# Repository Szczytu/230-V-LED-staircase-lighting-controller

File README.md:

# 230-V-LED-staircase-lighting-controller
Controller for a large staircase consisting of 3 parts, total 26 stairs on 230 V LED strips. The controller has a built-in twilight sensor, the sensitivity of which can be adjusted using a potentiometer.
The construction of the controller was due to an unusual staircase and the desire not to use a separate power supply for 12-24V LEDs 
# Schematic and project controller of 230V LED
The project schematic, sample 3D model and gerber file is in the folder "PCB_162x104mm_LED_STAIRS"
The project was made in KiCad 8.0.
## Schematic

## Simplified schematic

> [!IMPORTANT]
> 1 leg of the BT136 triac is connected to the PHASE of the LED strip. The 2nd leg of the BT136 triac is connected to the PHASE of the AC mains. The 3rd leg of the BT136 triac is connected to the gate of the power3061 controller.

> [!CAUTION]
> DO NOT SWAP THE CONNECTION FROM THE 1ST LEG WITH THE 2ND LEG OF THE BT-136 TRIAC BECAUSE IT WILL NOT WORK!

## 3D model

## Final efect of the controller
A universal Kradex Z112A plastic housing with dimensions of 186x136x40mm was used to enclose the PCB

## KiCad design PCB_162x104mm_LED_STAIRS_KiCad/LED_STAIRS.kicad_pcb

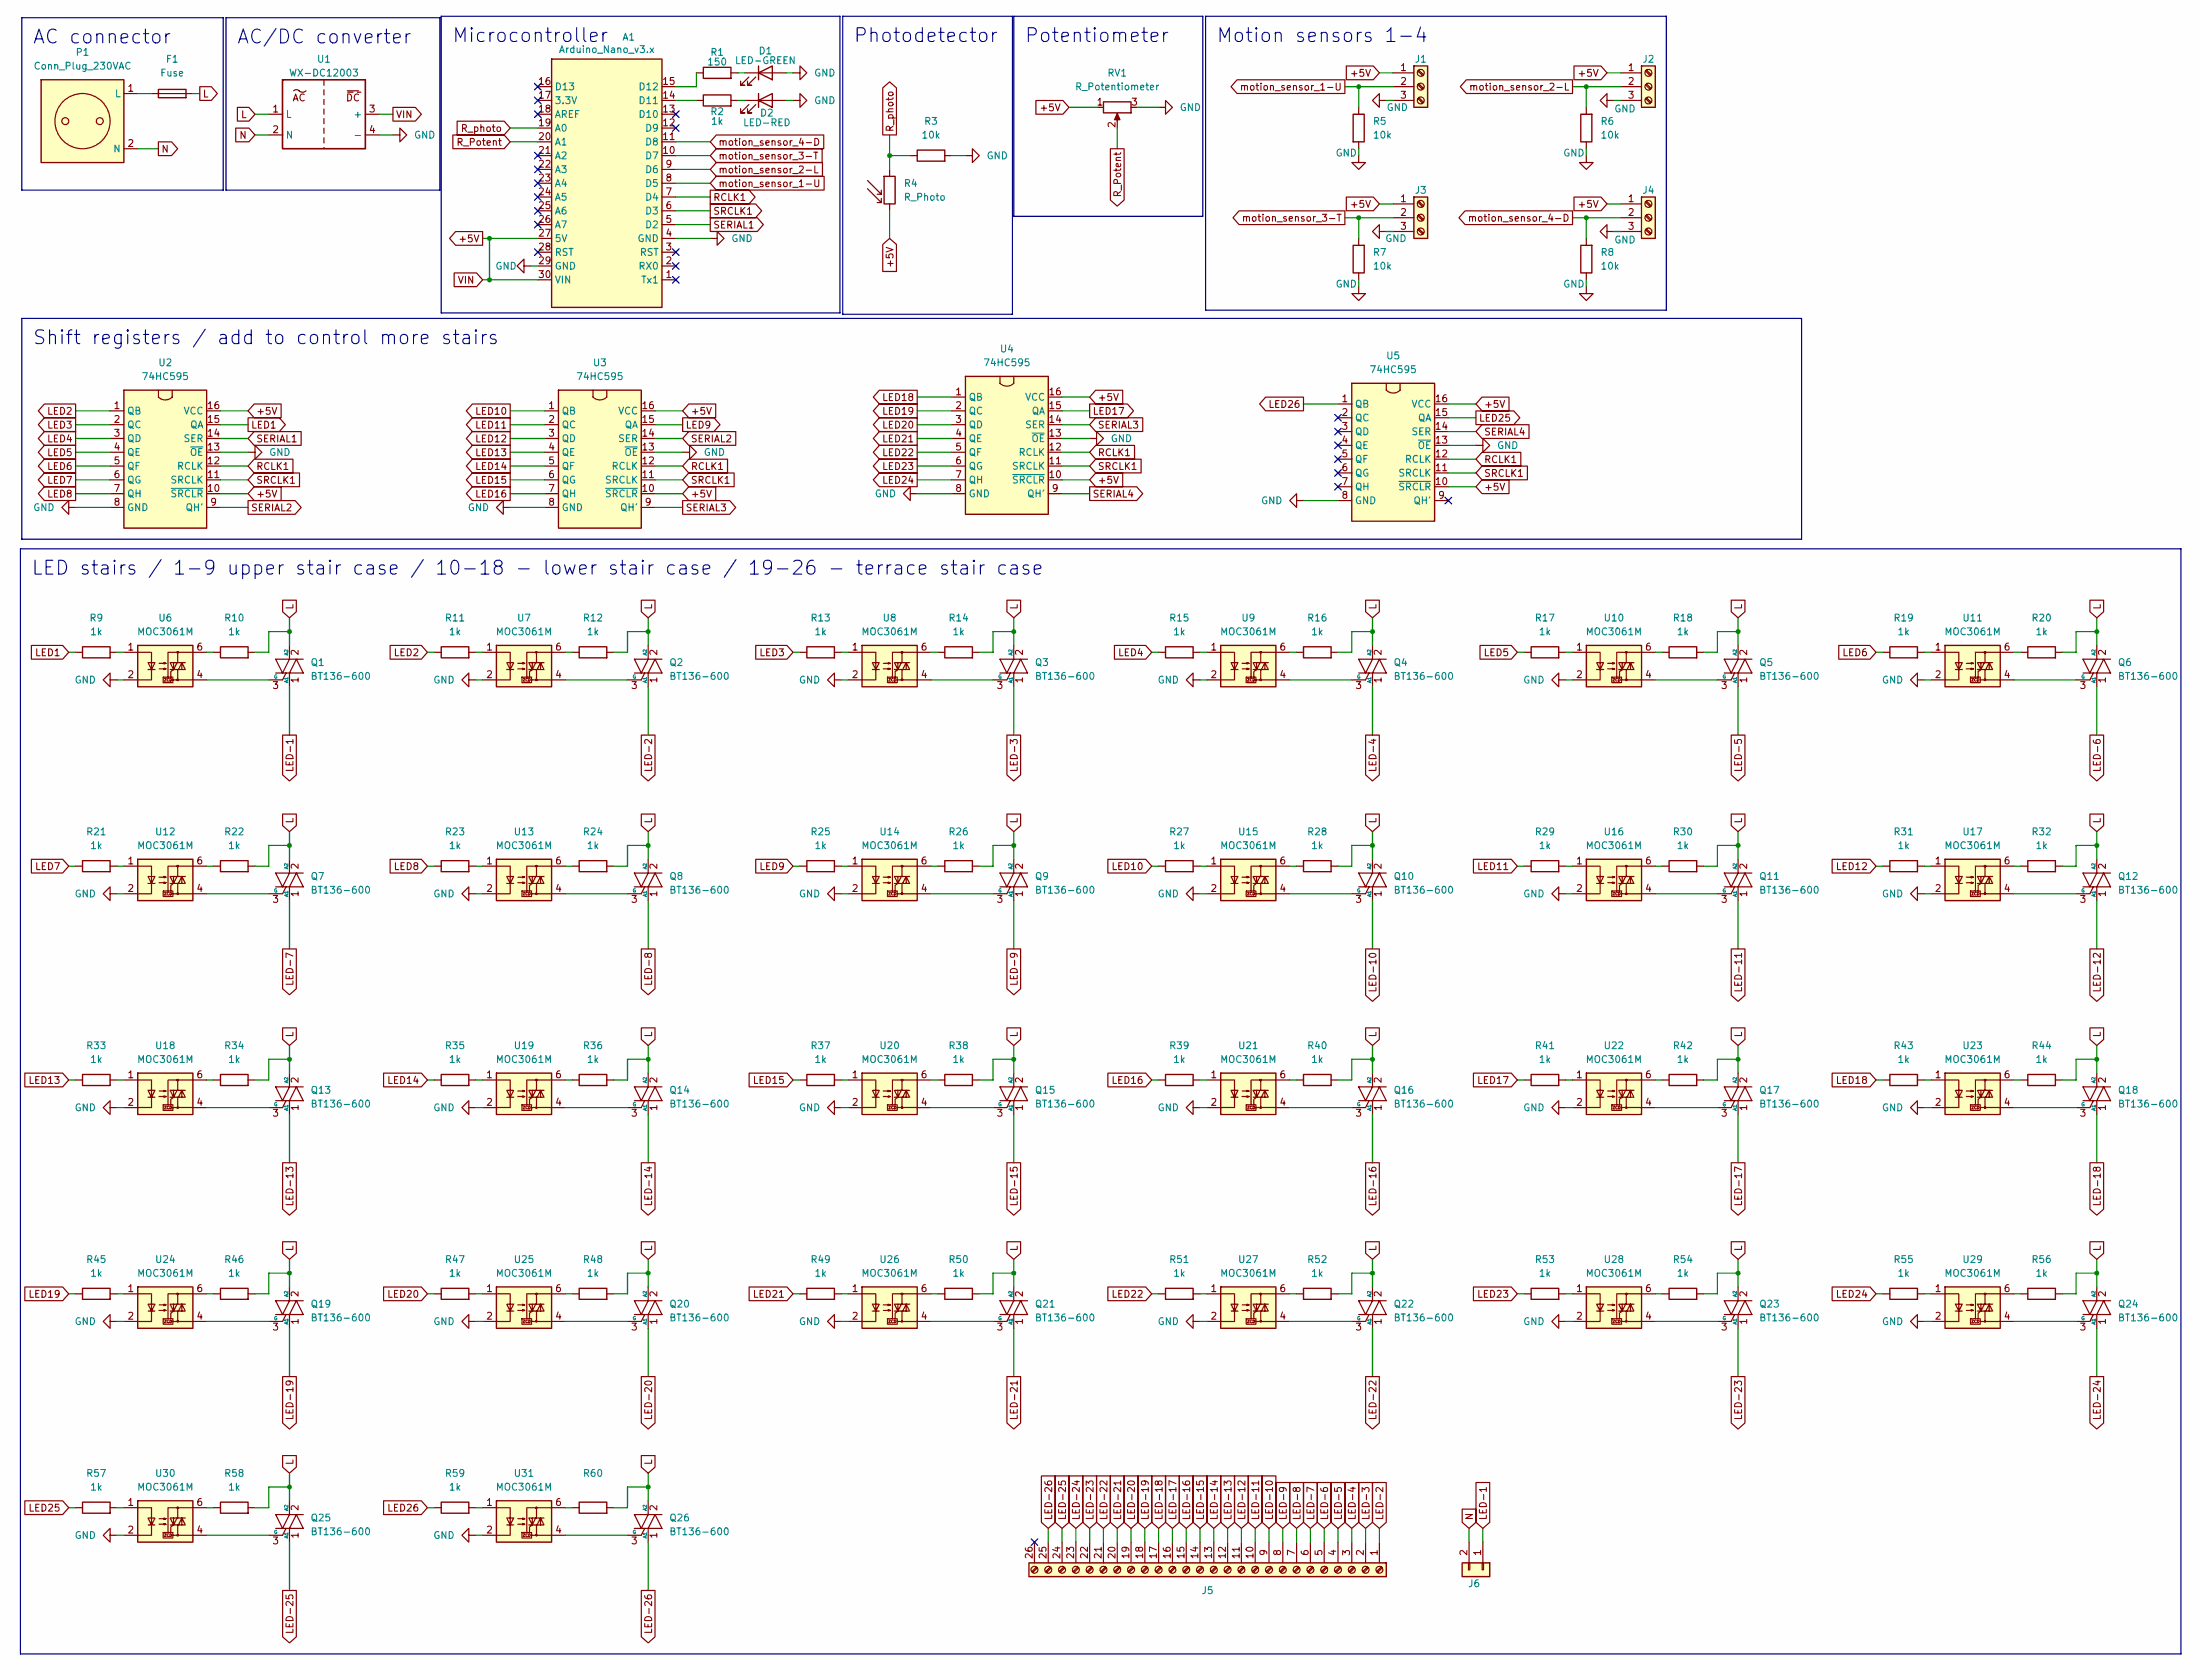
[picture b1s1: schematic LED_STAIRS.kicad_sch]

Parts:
A1: Arduino_Nano_v3.x; Arduino_Nano
D1: LED-GREEN; R_Axial_DIN0204_L3.6mm_D1.6mm_P2.54mm_Vertical
D2: LED-RED; R_Axial_DIN0204_L3.6mm_D1.6mm_P2.54mm_Vertical
F1: Fuse; Fuseholder_Cylinder-5x20mm_Stelvio-Kontek_PTF78_Horizontal_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
J1, J2, J3, J4: Screw_Terminal_01x03; terminalx03x2.5mmPitch
J5: Screw_Terminal_01x26; terminalx26x2.5mmPitch
J6: Conn_01x02; terminalx02x2.5mmPitch
P1: Conn_Plug_230VAC; terminalx02x2.5mmPitch
Q1, Q2, Q3, Q4, Q5, Q6, Q7, Q8, Q9, Q10, Q11, Q12, Q13, Q14, Q15, Q16, Q17, Q18, Q19, Q20, Q21, Q22, Q23, Q24, Q25, Q26: BT136-600; TO-220-3_Vertical
R1: 150; R_Axial_DIN0207_L6.3mm_D2.5mm_P10.16mm_Horizontal
R2, R9, R10, R11, R12, R13, R14, R15, R16, R17, R18, R19, R20, R21, R22, R23, R24, R25, R26, R27, R28, R29, R30, R31, R32, R33, R34, R35, R36, R37, R38, R39, R40, R41, R42, R43, R44, R45, R46, R47, R48, R49, R50, R51, R52, R53, R54, R55, R56, R57, R58, R59, R60: 1k; R_Axial_DIN0207_L6.3mm_D2.5mm_P10.16mm_Horizontal
R3, R5, R6, R7, R8: 10k; R_Axial_DIN0207_L6.3mm_D2.5mm_P10.16mm_Horizontal
R4: R_Photo; R_Axial_DIN0204_L3.6mm_D1.6mm_P2.54mm_Vertical
RV1: R_Potentiometer; Potentiometer_5k
U1: WX-DC12003
U2, U3, U4, U5: 74HC595; 74HC595N
U6, U7, U8, U9, U10, U11, U12, U13, U14, U15, U16, U17, U18, U19, U20, U21, U22, U23, U24, U25, U26, U27, U28, U29, U30, U31: MOC3061M; moc3021

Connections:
+5V: A1.27 (5V), A1.30 (VIN), J1.1, J2.1, J3.1, J4.1, R4.2, RV1.1, U1.3 (+), U2.10 (~SRCLR), U2.16 (VCC), U3.10 (~SRCLR), U3.16 (VCC), U4.10 (~SRCLR), U4.16 (VCC), U5.10 (~SRCLR), U5.16 (VCC); also elsewhere on the board
GND: A1.4 (GND), A1.29 (GND), D1.2 (A), D2.2 (A), J1.3, J2.3, J3.3, J4.3, R3.2, R5.2, R6.1, R7.1, R8.1, RV1.3, U1.4 (-), U2.8 (GND), U2.13 (~OE), U3.8 (GND), U3.13 (~OE), U4.8 (GND), U4.13 (~OE), U5.8 (GND), U5.13 (~OE), U6.2, U7.2, U8.2, U9.2, U10.2, U11.2, U12.2, U13.2, U14.2, U15.2, U16.2, U17.2, U18.2, U19.2, U20.2, U21.2, U22.2, U23.2, U24.2, U25.2, U26.2, U27.2, U28.2, U29.2, U30.2, U31.2; also elsewhere on the board
L: F1.2, Q1.2 (A2), Q2.2 (A2), Q3.2 (A2), Q4.2 (A2), Q5.2 (A2), Q6.2 (A2), Q7.2 (A2), Q8.2 (A2), Q9.2 (A2), Q10.2 (A2), Q11.2 (A2), Q12.2 (A2), Q13.2 (A2), Q14.2 (A2), Q15.2 (A2), Q16.2 (A2), Q17.2 (A2), Q18.2 (A2), Q19.2 (A2), Q20.2 (A2), Q21.2 (A2), Q22.2 (A2), Q23.2 (A2), Q24.2 (A2), Q25.2 (A2), Q26.2 (A2), R10.2, R12.2, R14.2, R16.2, R18.2, R20.2, R22.2, R24.2, R26.2, R28.2, R30.2, R32.2, R34.2, R36.2, R38.2, R40.2, R42.2, R44.2, R46.2, R48.2, R50.2, R52.2, R54.2, R56.2, R58.2, R60.2, U1.1 (L)
LED1: R9.1, U2.15 (QA)
LED2: R11.1, U2.1 (QB)
LED3: R13.1, U2.2 (QC)
LED4: R15.1, U2.3 (QD)
LED5: R17.1, U2.4 (QE)
LED6: R19.1, U2.5 (QF)
LED7: R21.1, U2.6 (QG)
LED8: R23.1, U2.7 (QH)
LED9: R25.1, U3.15 (QA)
LED10: R27.1, U3.1 (QB)
LED11: R29.1, U3.2 (QC)
LED12: R31.1, U3.3 (QD)
LED13: R33.1, U3.4 (QE)
LED14: R35.1, U3.5 (QF)
LED15: R37.1, U3.6 (QG)
LED16: R39.1, U3.7 (QH)
LED17: R41.1, U4.15 (QA)
LED18: R43.1, U4.1 (QB)
LED19: R45.1, U4.2 (QC)
LED20: R47.1, U4.3 (QD)
LED21: R49.1, U4.4 (QE)
LED22: R51.1, U4.5 (QF)
LED23: R53.1, U4.6 (QG)
LED24: R55.1, U4.7 (QH)
LED25: R57.1, U5.15 (QA)
LED26: R59.1, U5.1 (QB)
LED-1: J6.1, Q1.1 (A1)
LED-2: J5.1, Q2.1 (A1)
LED-3: J5.2, Q3.1 (A1)
LED-4: J5.3, Q4.1 (A1)
LED-5: J5.4, Q5.1 (A1)
LED-6: J5.5, Q6.1 (A1)
LED-7: J5.6, Q7.1 (A1)
LED-8: J5.7, Q8.1 (A1)
LED-9: J5.8, Q9.1 (A1)
LED-10: J5.9, Q10.1 (A1)
LED-11: J5.10, Q11.1 (A1)
LED-12: J5.11, Q12.1 (A1)
LED-13: J5.12, Q13.1 (A1)
LED-14: J5.13, Q14.1 (A1)
LED-15: J5.14, Q15.1 (A1)
LED-16: J5.15, Q16.1 (A1)
LED-17: J5.16, Q17.1 (A1)
LED-18: J5.17, Q18.1 (A1)
LED-19: J5.18, Q19.1 (A1)
LED-20: J5.19, Q20.1 (A1)
LED-21: J5.20, Q21.1 (A1)
LED-22: J5.21, Q22.1 (A1)
LED-23: J5.22, Q23.1 (A1)
LED-24: J5.23, Q24.1 (A1)
LED-25: J5.24, Q25.1 (A1)
LED-26: J5.25, Q26.1 (A1)
N: J6.2, P1.2 (N), U1.2 (N); also elsewhere on the board
unnamed: A1.14 (D11), R2.1
unnamed: A1.15 (D12), R1.1
unnamed: D1.1 (K), R1.2
unnamed: D2.1 (K), R2.2
unnamed 60: F1.1, P1.1 (L); also elsewhere on the board
unnamed: Q1.3 (G), U6.4
unnamed: Q2.3 (G), U7.4
unnamed: Q3.3 (G), U8.4
unnamed: Q4.3 (G), U9.4
unnamed: Q5.3 (G), U10.4
unnamed: Q6.3 (G), U11.4
unnamed: Q7.3 (G), U12.4
unnamed: Q8.3 (G), U13.4
unnamed: Q9.3 (G), U14.4
unnamed: Q10.3 (G), U15.4
unnamed: Q11.3 (G), U16.4
unnamed: Q12.3 (G), U17.4
unnamed: Q13.3 (G), U18.4
unnamed: Q14.3 (G), U19.4
unnamed: Q15.3 (G), U20.4
unnamed: Q16.3 (G), U21.4
unnamed: Q17.3 (G), U22.4
unnamed: Q18.3 (G), U23.4
unnamed: Q19.3 (G), U24.4
unnamed: Q20.3 (G), U25.4
unnamed: Q21.3 (G), U26.4
unnamed: Q22.3 (G), U27.4
unnamed: Q23.3 (G), U28.4
unnamed: Q24.3 (G), U29.4
unnamed: Q25.3 (G), U30.4
unnamed: Q26.3 (G), U31.4
unnamed: R9.2, U6.1
unnamed: R10.1, U6.6
unnamed: R11.2, U7.1
unnamed: R12.1, U7.6
unnamed: R13.2, U8.1
unnamed: R14.1, U8.6
unnamed: R15.2, U9.1
unnamed: R16.1, U9.6
unnamed: R17.2, U10.1
unnamed: R18.1, U10.6
unnamed: R19.2, U11.1
unnamed: R20.1, U11.6
unnamed: R21.2, U12.1
unnamed: R22.1, U12.6
unnamed: R23.2, U13.1
unnamed: R24.1, U13.6
unnamed: R25.2, U14.1
unnamed: R26.1, U14.6
unnamed: R27.2, U15.1
unnamed: R28.1, U15.6
unnamed: R29.2, U16.1
unnamed: R30.1, U16.6
unnamed: R31.2, U17.1
unnamed: R32.1, U17.6
unnamed: R33.2, U18.1
unnamed: R34.1, U18.6
unnamed: R35.2, U19.1
unnamed: R36.1, U19.6
unnamed: R37.2, U20.1
unnamed: R38.1, U20.6
unnamed: R39.2, U21.1
unnamed: R40.1, U21.6
unnamed: R41.2, U22.1
unnamed: R42.1, U22.6
unnamed: R43.2, U23.1
unnamed: R44.1, U23.6
unnamed: R45.2, U24.1
unnamed: R46.1, U24.6
unnamed: R47.2, U25.1
unnamed: R48.1, U25.6
unnamed: R49.2, U26.1
unnamed: R50.1, U26.6
unnamed: R51.2, U27.1
unnamed: R52.1, U27.6
unnamed: R53.2, U28.1
unnamed: R54.1, U28.6
unnamed: R55.2, U29.1
unnamed: R56.1, U29.6
unnamed: R57.2, U30.1
unnamed: R58.1, U30.6
unnamed: R59.2, U31.1
unnamed: R60.1, U31.6
RCLK1: A1.7 (D4), U2.12 (RCLK), U3.12 (RCLK), U4.12 (RCLK), U5.12 (RCLK)
R_Potent: A1.20 (A1), RV1.2; also elsewhere on the board
R_photo: A1.19 (A0), R3.1, R4.1
SERIAL1: A1.5 (D2), U2.14 (SER)
SERIAL2: U2.9 (QH'), U3.14 (SER)
SERIAL3: U3.9 (QH'), U4.14 (SER)
SERIAL4: U4.9 (QH'), U5.14 (SER)
SRCLK1: A1.6 (D3), U2.11 (SRCLK), U3.11 (SRCLK), U4.11 (SRCLK), U5.11 (SRCLK)
motion_sensor_1-U: A1.8 (D5), J1.2, R5.1; also elsewhere on the board
motion_sensor_2-L: A1.9 (D6), J2.2, R6.2; also elsewhere on the board
motion_sensor_3-T: A1.10 (D7), J3.2, R7.2; also elsewhere on the board
motion_sensor_4-D: A1.11 (D8), J4.2, R8.2; also elsewhere on the board

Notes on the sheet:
Potentiometer
AC connector
LED stairs / 1-9 upper stair case / 10-18 - lower stair case / 19-26 - terrace stair case
AC/DC converter
Microcontroller
Motion sensors 1-4
Shift registers / add to control more stairs
Photodetector

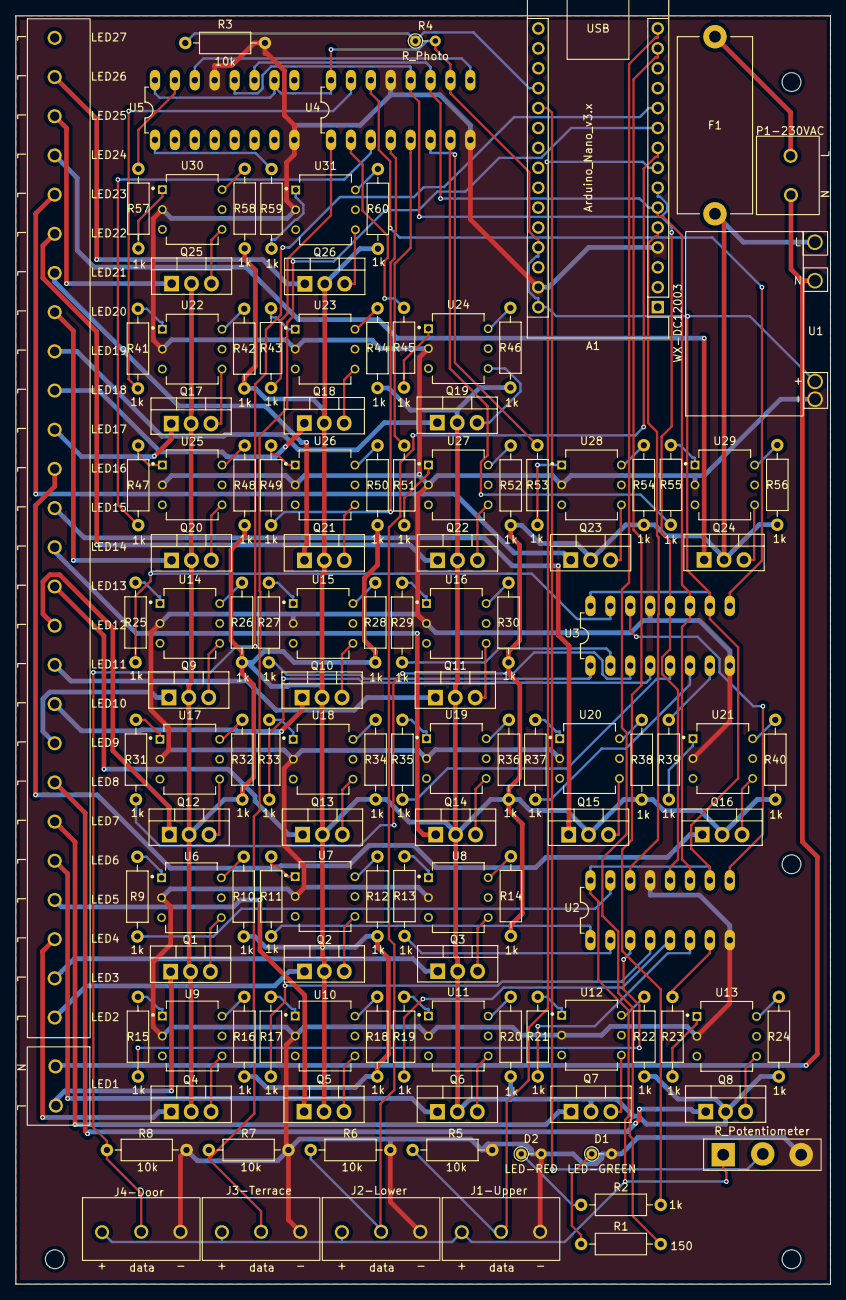
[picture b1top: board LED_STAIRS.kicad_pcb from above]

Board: 2 copper layers, 103.9 x 161.8 mm, 129 parts (0 on the bottom side), 151 nets.

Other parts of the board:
J1-Upper, J2-Lower, J3-Terrace, J4-Door: Screw_Terminal_01x03; terminalx03x2.5mmPitch
P1-230VAC: Conn_Plug_230VAC; terminalx02x2.5mmPitch
R_Potentiometer: R_Potentiometer; Potentiometer_5k

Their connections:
+5V: J1-Upper.1, J2-Lower.1, J3-Terrace.1, J4-Door.1, R_Potentiometer.1; also elsewhere on the board
GND: J1-Upper.3, J2-Lower.3, J3-Terrace.3, J4-Door.3, R_Potentiometer.3; also elsewhere on the board
N: P1-230VAC.2 (N); also elsewhere on the board
unnamed 60: P1-230VAC.1 (L); also elsewhere on the board
R_Potent: R_Potentiometer.2; also elsewhere on the board
motion_sensor_1-U: J1-Upper.2; also elsewhere on the board
motion_sensor_2-L: J2-Lower.2; also elsewhere on the board
motion_sensor_3-T: J3-Terrace.2; also elsewhere on the board
motion_sensor_4-D: J4-Door.2; also elsewhere on the board

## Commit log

2025-01-02 Update LED_STAIRS.ino
    Add green and red LED
